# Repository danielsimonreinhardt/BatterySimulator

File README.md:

# BatterySimulator

Zellspannungs-Simulator für Tests von Batteriemanagement-Steuergeräten: 14 isolierte Zellkanäle (je 0–5 V, bis 0,5 A, zu einem
Stapel kaskadiert), ein Master mit S32K146, Bedienung über Drehgeber, Anzeige und Taster oder ferngesteuert per CAN (500 kbit/s).

| Ordner | Inhalt |
|---|---|
| [`Hardware/`](Hardware/) | Schaltpläne und Platinen (KiCad): Master, Zellkanal, Rückwand, Versorgung, dazu die Stückliste. |
| [`Firmware/`](Firmware/) | Firmware des Masters als neXtBSW-Kundenprojekt (`battsim_master`), mit Tests, Gerätetermin-Protokollen und Sicherheitshinweisen. |
| [`Doku/`](Doku/) | Analyse der alten Hard- und Firmware, Konzept, Reviews und Entscheidungen, CAN-Verhalten. Einstieg: [`Doku/README.md`](Doku/README.md). |

## Firmware klonen und bauen

neXtBSW liegt als Untermodul in `Firmware/nextbsw` (Repository `neXtBSW_development`, **privat**: ohne Zugriff schlägt das
Klonen des Untermoduls fehl). Auf Windows zählt die Pfadlänge (der längste Objektpfad des Baus misst gut 240 von 260 Zeichen),
deshalb dieses Repository möglichst weit oben im Dateisystem klonen, z. B. nach `C:\BatterySimulator`.

```sh
git clone --recurse-submodules https://github.com/danielsimonreinhardt/BatterySimulator.git C:/BatterySimulator
cd C:/BatterySimulator/Firmware
python nextbsw/tools/setup venv .
cmake --preset battsim-master
cmake --build --preset battsim-master
```

Weiter in [`Firmware/README.md`](Firmware/README.md).

## Lizenz

* **Firmware und Dokumentation** (`Firmware/`, `Doku/`): Apache License 2.0, siehe [`LICENSE`](LICENSE). Das Untermodul `Firmware/nextbsw` ist ein eigenes
  Repository und hat seine eigenen Bedingungen.
* **Hardware** (`Hardware/`): CERN Open Hardware Licence Version 2 – Permissive (CERN-OHL-P-2.0), siehe [`Hardware/LICENSE`](Hardware/LICENSE).

Schaltpläne und Platinen enthalten Symbole und Footprints aus den offiziellen KiCad-Bibliotheken (Lizenz: CC-BY-SA 4.0 mit der
KiCad-Ausnahme für Entwürfe, die diese Bibliotheken nur verwenden); sie bleiben dadurch unter deren Bedingungen, der Entwurf selbst unter CERN-OHL-P-2.0.

**Aufdruck auf den Platinen:** Auf den Platinen `BattSimMaster`, `BattSim_V1` und `BattSim_Supply` steht der Text „CREATED 11/2024 – ALL RIGHTS RESERVED“.
Er gilt nicht mehr: Für die Entwürfe in `Hardware/` gilt die CERN-OHL-P-2.0, auch wenn der Aufdruck auf bereits gefertigten Platinen etwas anderes sagt. Der Aufdruck wird mit der
nächsten Platinen-Revision angepasst; die KiCad-Quellen sind bis dahin unverändert.

## Stand

Firmware und Doku sind der Arbeitsstand der Entwicklung; ein Release gibt es nicht. Ein Gerät darf nur nach den
Sicherheitshinweisen in `Firmware/doc/` und `Doku/` angeschlossen und geflasht werden (kein Prüfling und keine Last an den
Zellklemmen beim Flashen).

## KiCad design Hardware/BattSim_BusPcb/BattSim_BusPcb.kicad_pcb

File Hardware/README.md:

# Hardware

KiCad-Quellen des Batterie-Simulators (je Ordner ein KiCad-Projekt) und die Stückliste. Lizenz: CERN-OHL-P-2.0, siehe [`LICENSE`](LICENSE).

| Ordner | Inhalt |
|---|---|
| `BattSimMaster/` | Master mit S32K146 (Blätter `BattSimMaster` und `MCU`) |
| `BattSim_V1/` | Zellkanal |
| `BattSim_BusPcb/` | Rückwand |
| `BattSim_Supply/` | Versorgung (230 V → 48 V → 5 V) |
| `BOM_gesamt.xlsx` | Stückliste aller Baugruppen |

Übernommen sind nur die Quellen (`.kicad_pro`, `.kicad_sch`, `.kicad_pcb`). Nicht dabei sind die 3D-Modelle (`.step`), die Fertigungsdaten (Gerber),
die KiCad-Sicherungen, die Simulationsdateien und Zwischenspeicher; die 3D-Modelle der Bauteile kommen aus den KiCad-Standardbibliotheken.
Die Quellen werden vom Nutzer außerhalb dieses Repositorys gepflegt und hier bei Bedarf nachgezogen.

Beschreibung der Hardware und Sicherheitsbefunde: [`../Doku/hardware-system.html`](../Doku/hardware-system.html) und
[`../Doku/hardware-zellkanal.html`](../Doku/hardware-zellkanal.html).

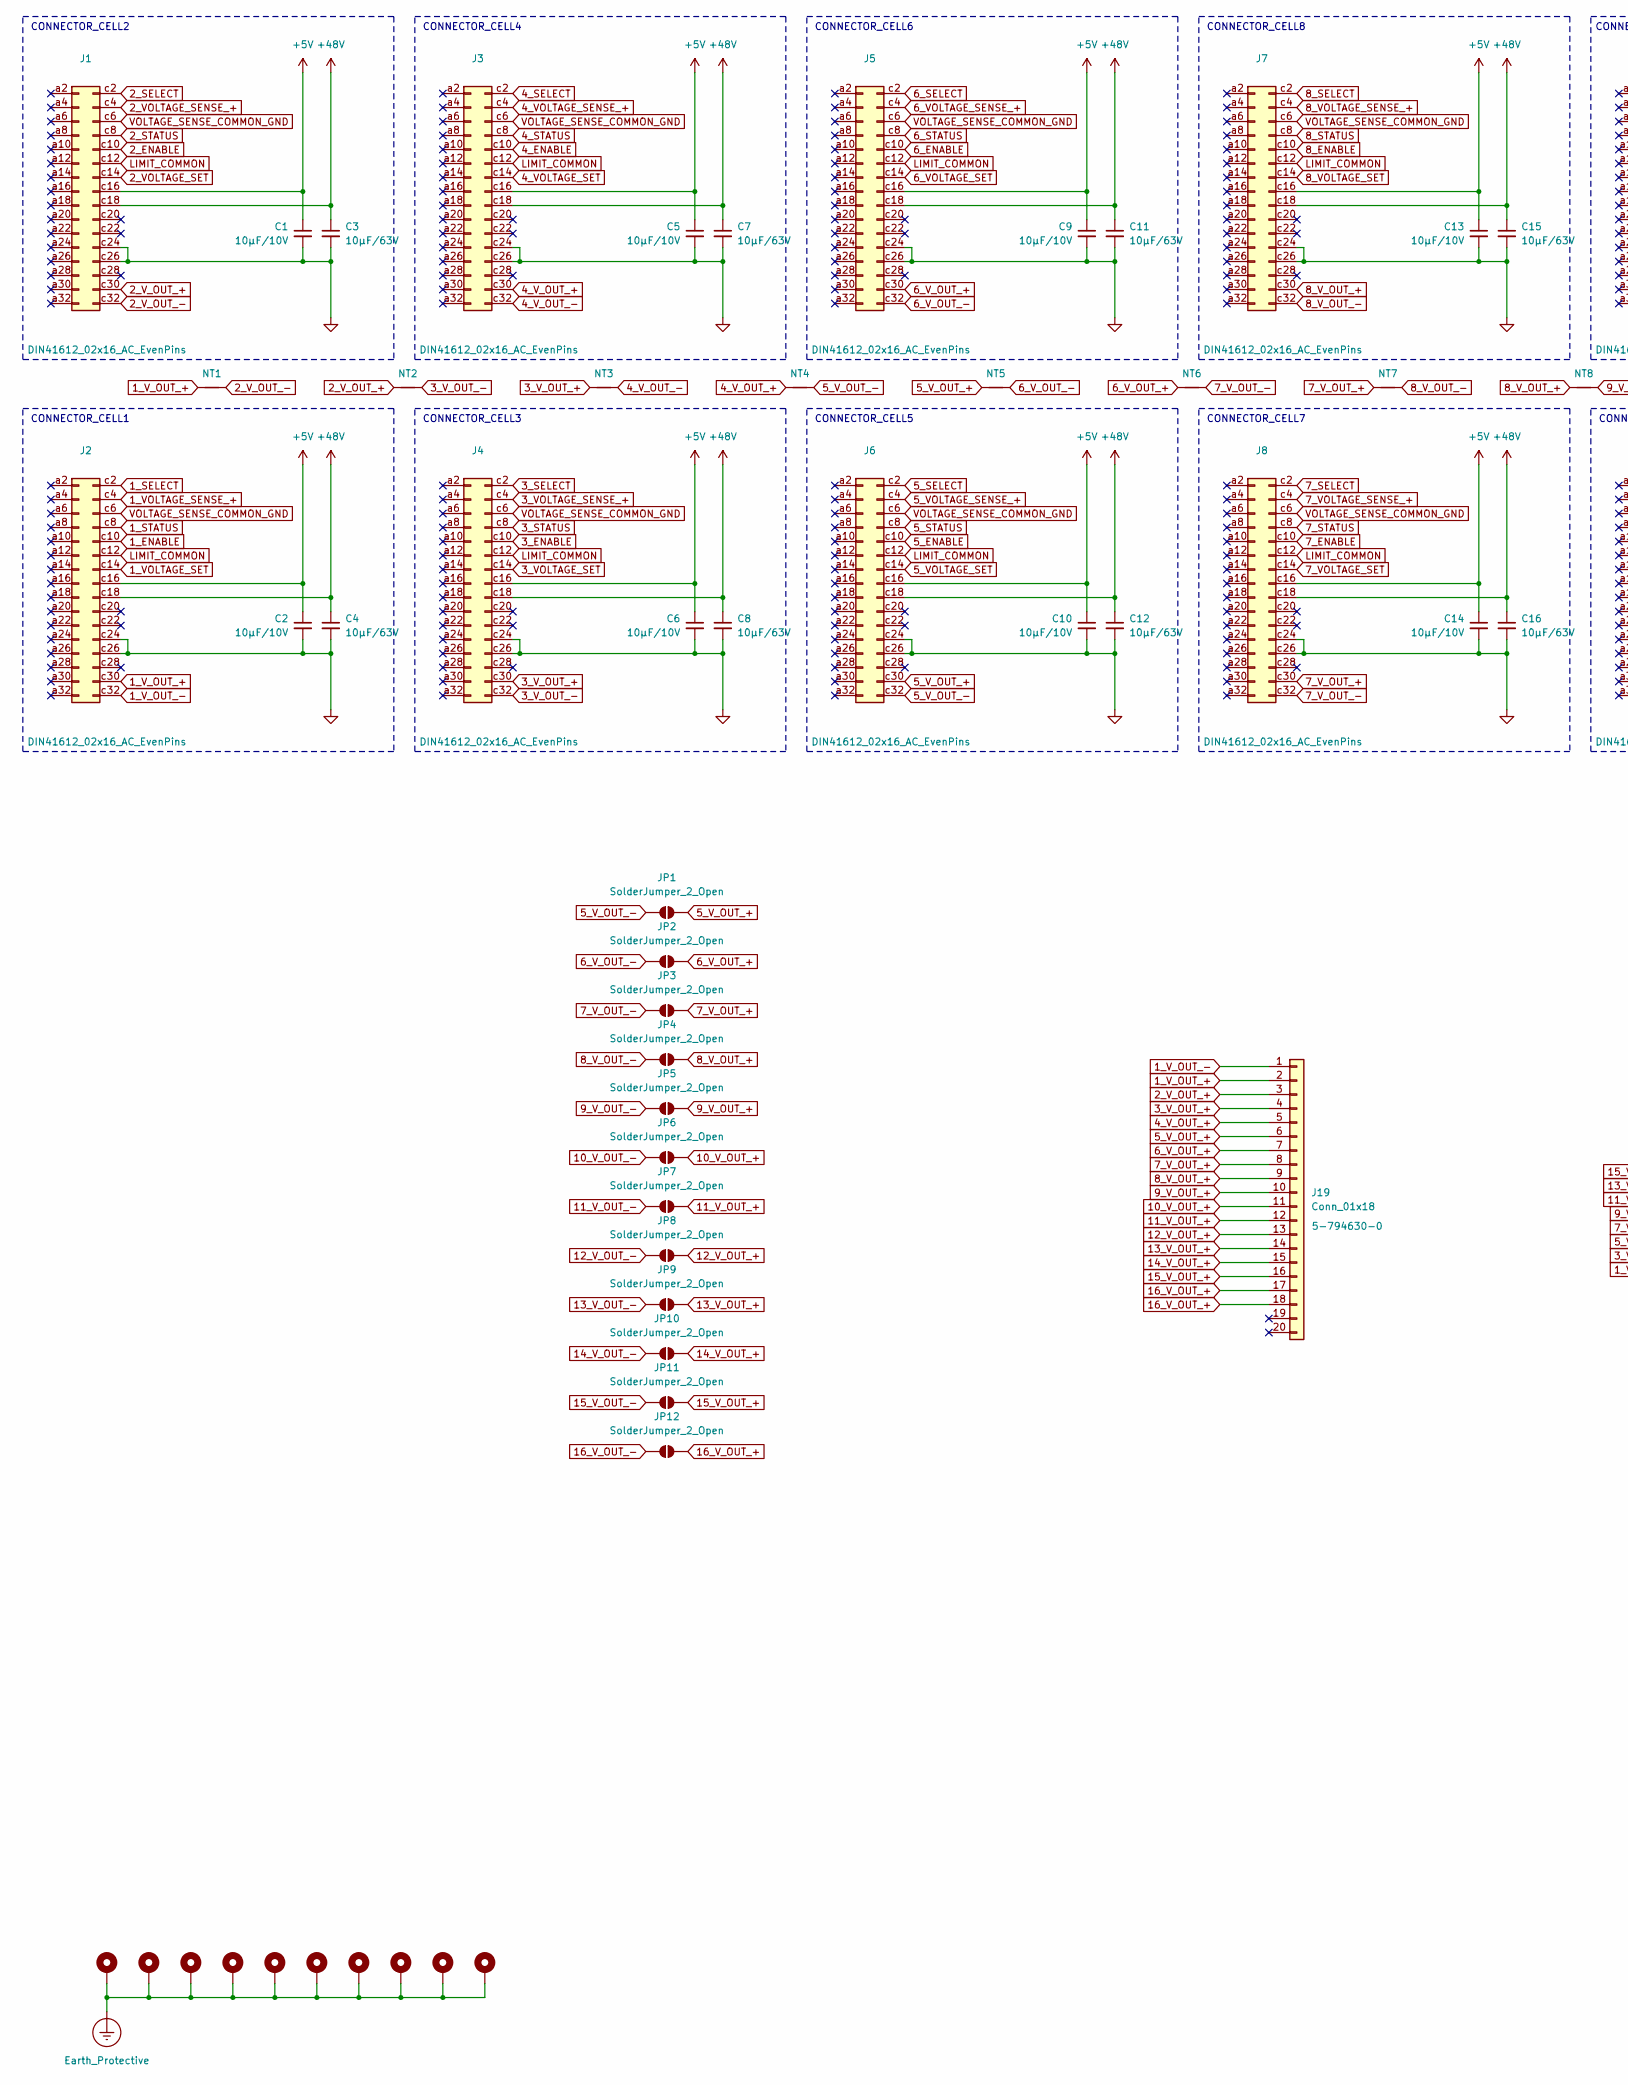
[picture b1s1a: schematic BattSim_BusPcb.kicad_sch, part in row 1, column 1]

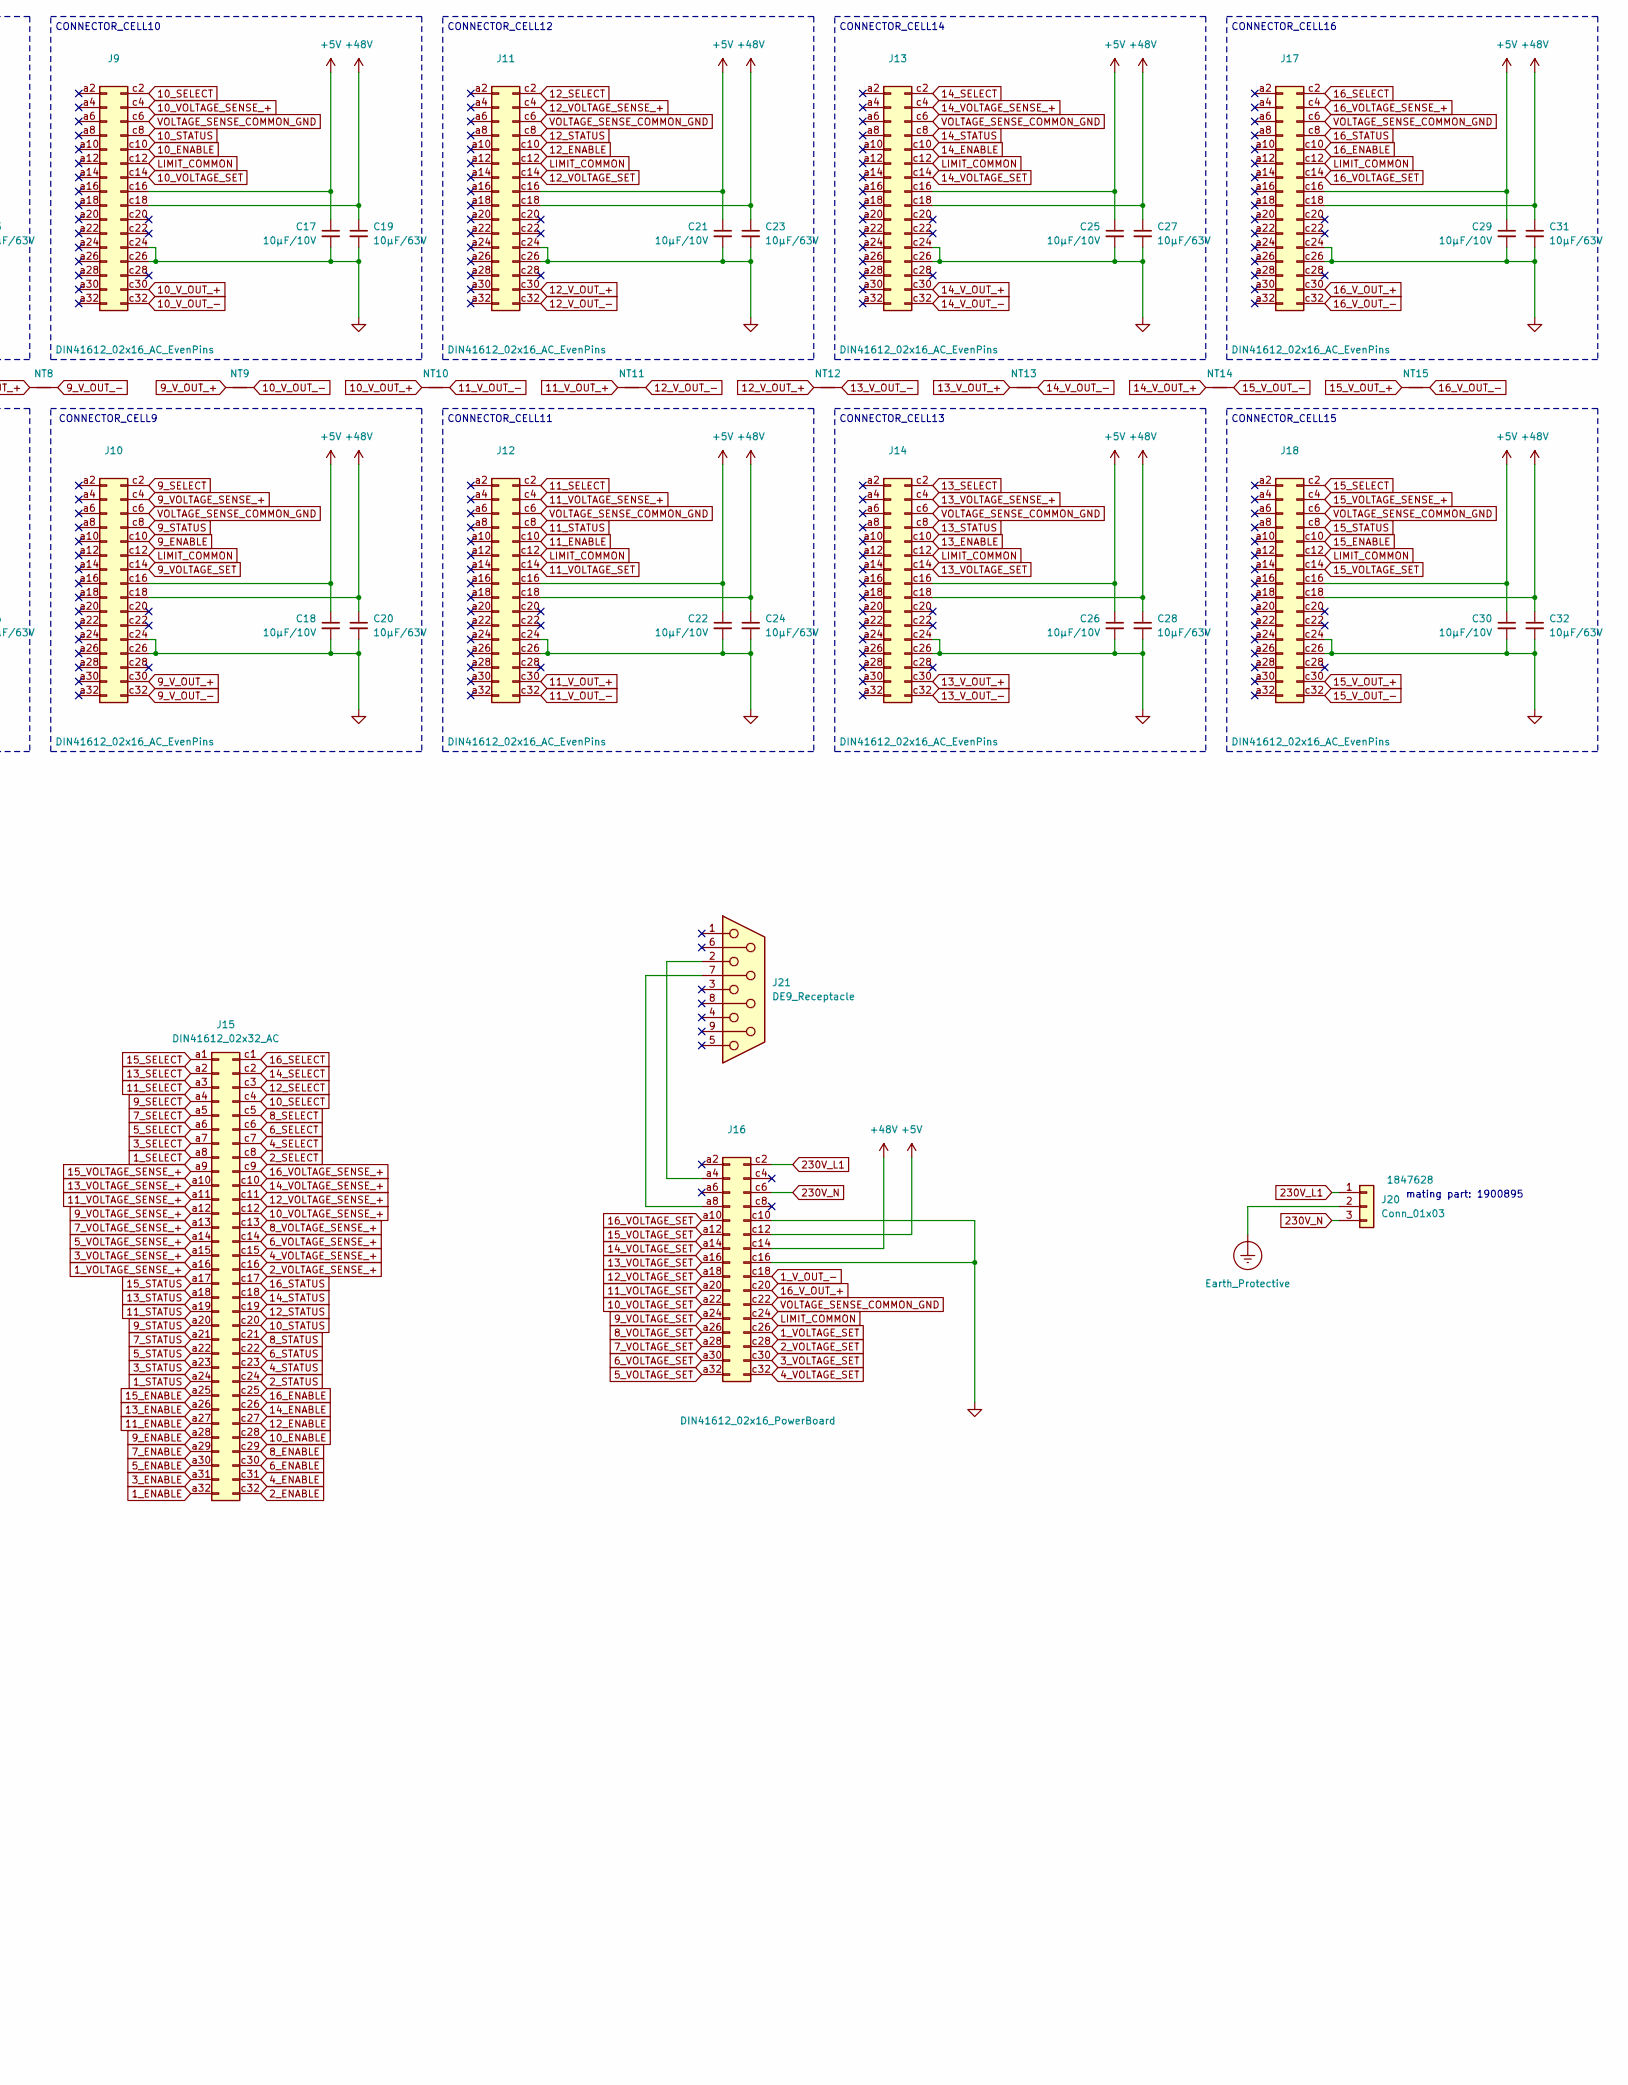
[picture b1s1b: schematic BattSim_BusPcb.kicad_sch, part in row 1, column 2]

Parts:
C1, C2, C5, C6, C9, C10, C13, C14, C17, C18, C21, C22, C25, C26, C29, C30: 10µF/10V; C_0805_2012Metric
C3, C4, C7, C8, C11, C12, C15, C16, C19, C20, C23, C24, C27, C28, C31, C32: 10µF/63V; C_1812_4532Metric
H1, H2, H3, H4, H5, H6, H7, H8, H9, H10: MountingHole_Pad; MountingHole_4.3x6.2mm_M4_Pad_Via
J1, J2, J3, J4, J5, J6, J7, J8, J9, J10, J11, J12, J13, J14, J17, J18: DIN41612_02x16_AC_EvenPins; DIN41612_C_2x16_Female_Vertical_THT
J15: DIN41612_02x32_AC; DIN41612_C_2x32_Female_Vertical_THT
J16: DIN41612_02x16_PowerBoard; DIN41612_C_2x16_Female_Vertical_THT
J19: Conn_01x18; 5-794630-0
J20: Conn_01x03; PhoenixContact_MCV_1,5_3-GF-5.08_1x03_P5.08mm_Vertical_Thre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
J21: DE9_Receptacle; DSUB-9_Female_Vertical_P2.77x2.84mm_MountingHoles
JP1, JP2, JP3, JP4, JP5, JP6, JP7, JP8, JP9, JP10, JP11, JP12: SolderJumper_2_Open; SolderJumper-2_P1.3mm_Open_RoundedPad1.0x1.5mm
NT1, NT2, NT3, NT4, NT5, NT6, NT7, NT8, NT9, NT10, NT11, NT12, NT13, NT14, NT15: NetTie_2; NetTie-2_THT_Pad1.0mm

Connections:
1_ENABLE: J2.c10, J15.a32
1_SELECT: J2.c2, J15.a8
1_STATUS: J2.c8, J15.a24
1_VOLTAGE_SENSE_+: J2.c4, J15.a16
1_VOLTAGE_SET: J2.c14, J16.c26
1_V_OUT_+: J2.c30, J19.2, NT1.1
1_V_OUT_-: J2.c32, J16.c18, J19.1
2_ENABLE: J1.c10, J15.c32
2_SELECT: J1.c2, J15.c8
2_STATUS: J1.c8, J15.c24
2_VOLTAGE_SENSE_+: J1.c4, J15.c16
2_VOLTAGE_SET: J1.c14, J16.c28
2_V_OUT_+: J1.c30, J19.3, NT2.1
2_V_OUT_-: J1.c32, NT1.2
3_ENABLE: J4.c10, J15.a31
3_SELECT: J4.c2, J15.a7
3_STATUS: J4.c8, J15.a23
3_VOLTAGE_SENSE_+: J4.c4, J15.a15
3_VOLTAGE_SET: J4.c14, J16.c30
3_V_OUT_+: J4.c30, J19.4, NT3.1
3_V_OUT_-: J4.c32, NT2.2
4_ENABLE: J3.c10, J15.c31
4_SELECT: J3.c2, J15.c7
4_STATUS: J3.c8, J15.c23
4_VOLTAGE_SENSE_+: J3.c4, J15.c15
4_VOLTAGE_SET: J3.c14, J16.c32
4_V_OUT_+: J3.c30, J19.5, NT4.1
4_V_OUT_-: J3.c32, NT3.2
5_ENABLE: J6.c10, J15.a30
5_SELECT: J6.c2, J15.a6
5_STATUS: J6.c8, J15.a22
5_VOLTAGE_SENSE_+: J6.c4, J15.a14
5_VOLTAGE_SET: J6.c14, J16.a32
5_V_OUT_+: J6.c30, J19.6, JP1.2 (B), NT5.1
5_V_OUT_-: J6.c32, JP1.1 (A), NT4.2
6_ENABLE: J5.c10, J15.c30
6_SELECT: J5.c2, J15.c6
6_STATUS: J5.c8, J15.c22
6_VOLTAGE_SENSE_+: J5.c4, J15.c14
6_VOLTAGE_SET: J5.c14, J16.a30
6_V_OUT_+: J5.c30, J19.7, JP2.2 (B), NT6.1
6_V_OUT_-: J5.c32, JP2.1 (A), NT5.2
7_ENABLE: J8.c10, J15.a29
7_SELECT: J8.c2, J15.a5
7_STATUS: J8.c8, J15.a21
7_VOLTAGE_SENSE_+: J8.c4, J15.a13
7_VOLTAGE_SET: J8.c14, J16.a28
7_V_OUT_+: J8.c30, J19.8, JP3.2 (B), NT7.1
7_V_OUT_-: J8.c32, JP3.1 (A), NT6.2
8_ENABLE: J7.c10, J15.c29
8_SELECT: J7.c2, J15.c5
8_STATUS: J7.c8, J15.c21
8_VOLTAGE_SENSE_+: J7.c4, J15.c13
8_VOLTAGE_SET: J7.c14, J16.a26
8_V_OUT_+: J7.c30, J19.9, JP4.2 (B), NT8.1
8_V_OUT_-: J7.c32, JP4.1 (A), NT7.2
9_ENABLE: J10.c10, J15.a28
9_SELECT: J10.c2, J15.a4
9_STATUS: J10.c8, J15.a20
9_VOLTAGE_SENSE_+: J10.c4, J15.a12
9_VOLTAGE_SET: J10.c14, J16.a24
9_V_OUT_+: J10.c30, J19.10, JP5.2 (B), NT9.1
9_V_OUT_-: J10.c32, JP5.1 (A), NT8.2
10_ENABLE: J9.c10, J15.c28
10_SELECT: J9.c2, J15.c4
10_STATUS: J9.c8, J15.c20
10_VOLTAGE_SENSE_+: J9.c4, J15.c12
10_VOLTAGE_SET: J9.c14, J16.a22
10_V_OUT_+: J9.c30, J19.11, JP6.2 (B), NT10.1
10_V_OUT_-: J9.c32, JP6.1 (A), NT9.2
11_ENABLE: J12.c10, J15.a27
11_SELECT: J12.c2, J15.a3
11_STATUS: J12.c8, J15.a19
11_VOLTAGE_SENSE_+: J12.c4, J15.a11
11_VOLTAGE_SET: J12.c14, J16.a20
11_V_OUT_+: J12.c30, J19.12, JP7.2 (B), NT11.1
11_V_OUT_-: J12.c32, JP7.1 (A), NT10.2
12_ENABLE: J11.c10, J15.c27
12_SELECT: J11.c2, J15.c3
12_STATUS: J11.c8, J15.c19
12_VOLTAGE_SENSE_+: J11.c4, J15.c11
12_VOLTAGE_SET: J11.c14, J16.a18
12_V_OUT_+: J11.c30, J19.13, JP8.2 (B), NT12.1
12_V_OUT_-: J11.c32, JP8.1 (A), NT11.2
13_ENABLE: J14.c10, J15.a26
13_SELECT: J14.c2, J15.a2
13_STATUS: J14.c8, J15.a18
13_VOLTAGE_SENSE_+: J14.c4, J15.a10
13_VOLTAGE_SET: J14.c14, J16.a16
13_V_OUT_+: J14.c30, J19.14, JP9.2 (B), NT13.1
13_V_OUT_-: J14.c32, JP9.1 (A), NT12.2
14_ENABLE: J13.c10, J15.c26
14_SELECT: J13.c2, J15.c2
14_STATUS: J13.c8, J15.c18
14_VOLTAGE_SENSE_+: J13.c4, J15.c10
14_VOLTAGE_SET: J13.c14, J16.a14
14_V_OUT_+: J13.c30, J19.15, JP10.2 (B), NT14.1
14_V_OUT_-: J13.c32, JP10.1 (A), NT13.2
15_ENABLE: J15.a25, J18.c10
15_SELECT: J15.a1, J18.c2
15_STATUS: J15.a17, J18.c8
15_VOLTAGE_SENSE_+: J15.a9, J18.c4
15_VOLTAGE_SET: J16.a12, J18.c14
15_V_OUT_+: J18.c30, J19.16, JP11.2 (B), NT15.1
15_V_OUT_-: J18.c32, JP11.1 (A), NT14.2
16_ENABLE: J15.c25, J17.c10
16_SELECT: J15.c1, J17.c2
16_STATUS: J15.c17, J17.c8
16_VOLTAGE_SENSE_+: J15.c9, J17.c4
16_VOLTAGE_SET: J16.a10, J17.c14
16_V_OUT_+: J16.c20, J17.c30, J19.17, J19.18, JP12.2 (B)
16_V_OUT_-: J17.c32, JP12.1 (A), NT15.2
230V_L1: J16.c2, J20.1
230V_N: J16.c6, J20.3
+5V: C1.1, C2.1, C5.1, C6.1, C9.1, C10.1, C13.1, C14.1, C17.1, C18.1, C21.1, C22.1, C25.1, C26.1, C29.1, C30.1, J1.c16, J2.c16, J3.c16, J4.c16, J5.c16, J6.c16, J7.c16, J8.c16, J9.c16, J10.c16, J11.c16, J12.c16, J13.c16, J14.c16, J16.c12, J17.c16, J18.c16
+48V: C3.1, C4.1, C7.1, C8.1, C11.1, C12.1, C15.1, C16.1, C19.1, C20.1, C23.1, C24.1, C27.1, C28.1, C31.1, C32.1, J1.c18, J2.c18, J3.c18, J4.c18, J5.c18, J6.c18, J7.c18, J8.c18, J9.c18, J10.c18, J11.c18, J12.c18, J13.c18, J14.c18, J16.c14, J17.c18, J18.c18
Earth_Protective: H1.1, H2.1, H3.1, H4.1, H5.1, H6.1, H7.1, H8.1, H9.1, H10.1, J20.2
GND: C1.2, C2.2, C3.2, C4.2, C5.2, C6.2, C7.2, C8.2, C9.2, C10.2, C11.2, C12.2, C13.2, C14.2, C15.2, C16.2, C17.2, C18.2, C19.2, C20.2, C21.2, C22.2, C23.2, C24.2, C25.2, C26.2, C27.2, C28.2, C29.2, C30.2, C31.2, C32.2, J1.c24, J1.c26, J2.c24, J2.c26, J3.c24, J3.c26, J4.c24, J4.c26, J5.c24, J5.c26, J6.c24, J6.c26, J7.c24, J7.c26, J8.c24, J8.c26, J9.c24, J9.c26, J10.c24, J10.c26, J11.c24, J11.c26, J12.c24, J12.c26, J13.c24, J13.c26, J14.c24, J14.c26, J16.c10, J16.c16, J17.c24, J17.c26, J18.c24, J18.c26
LIMIT_COMMON: J1.c12, J2.c12, J3.c12, J4.c12, J5.c12, J6.c12, J7.c12, J8.c12, J9.c12, J10.c12, J11.c12, J12.c12, J13.c12, J14.c12, J16.c24, J17.c12, J18.c12
unnamed: J16.a4, J21.2
unnamed: J16.a8, J21.7
VOLTAGE_SENSE_COMMON_GND: J1.c6, J2.c6, J3.c6, J4.c6, J5.c6, J6.c6, J7.c6, J8.c6, J9.c6, J10.c6, J11.c6, J12.c6, J13.c6, J14.c6, J16.c22, J17.c6, J18.c6

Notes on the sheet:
CONNECTOR_CELL12
CONNECTOR_CELL15
CONNECTOR_CELL2
CONNECTOR_CELL10
mating part: 1900895
CONNECTOR_CELL7
CONNECTOR_CELL8
CONNECTOR_CELL3
CONNECTOR_CELL4
CONNECTOR_CELL1
CONNECTOR_CELL6
CONNECTOR_CELL11
CONNECTOR_CELL9
CONNECTOR_CELL14
CONNECTOR_CELL16
CONNECTOR_CELL5
CONNECTOR_CELL13

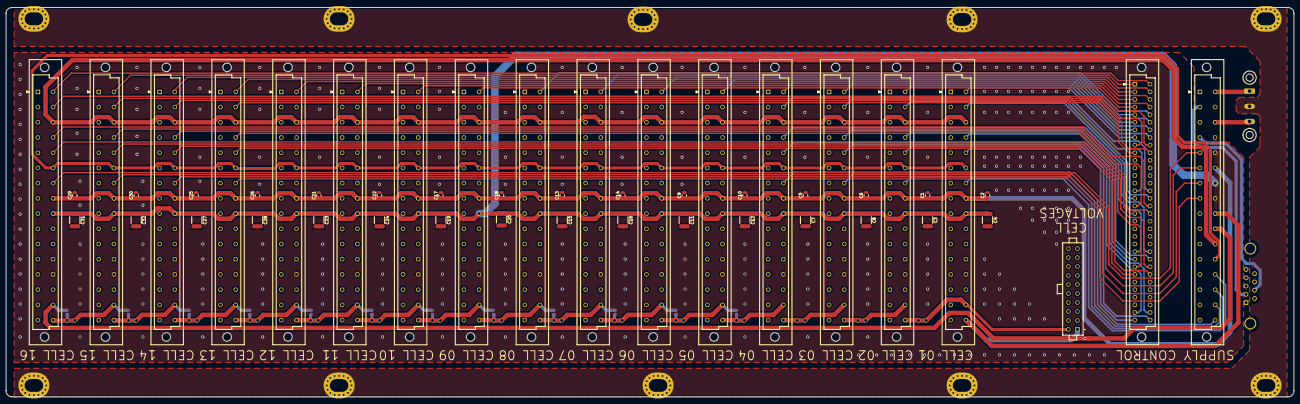
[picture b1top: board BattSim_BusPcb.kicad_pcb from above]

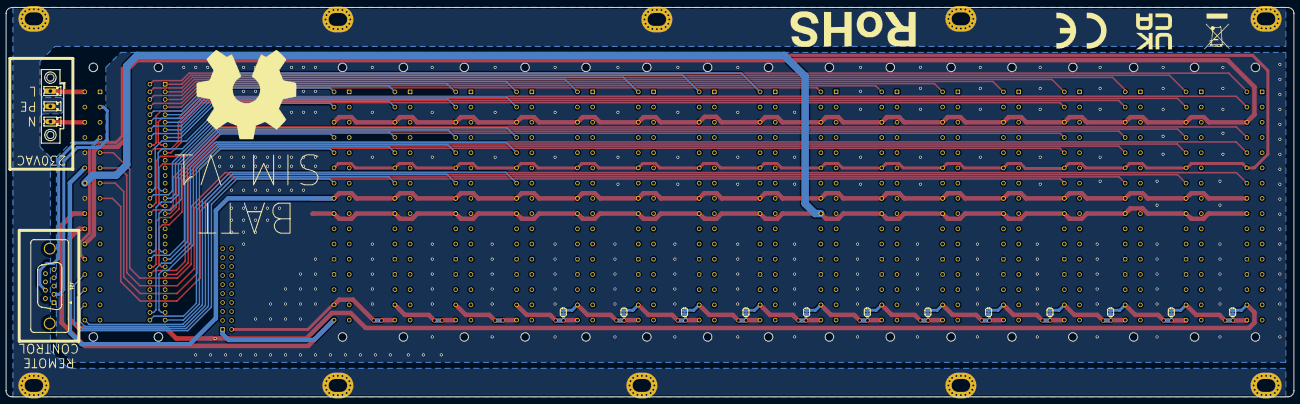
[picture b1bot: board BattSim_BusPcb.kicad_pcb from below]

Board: 4 copper layers, 430.0 x 130.0 mm, 90 parts (14 on the bottom side), 122 nets.

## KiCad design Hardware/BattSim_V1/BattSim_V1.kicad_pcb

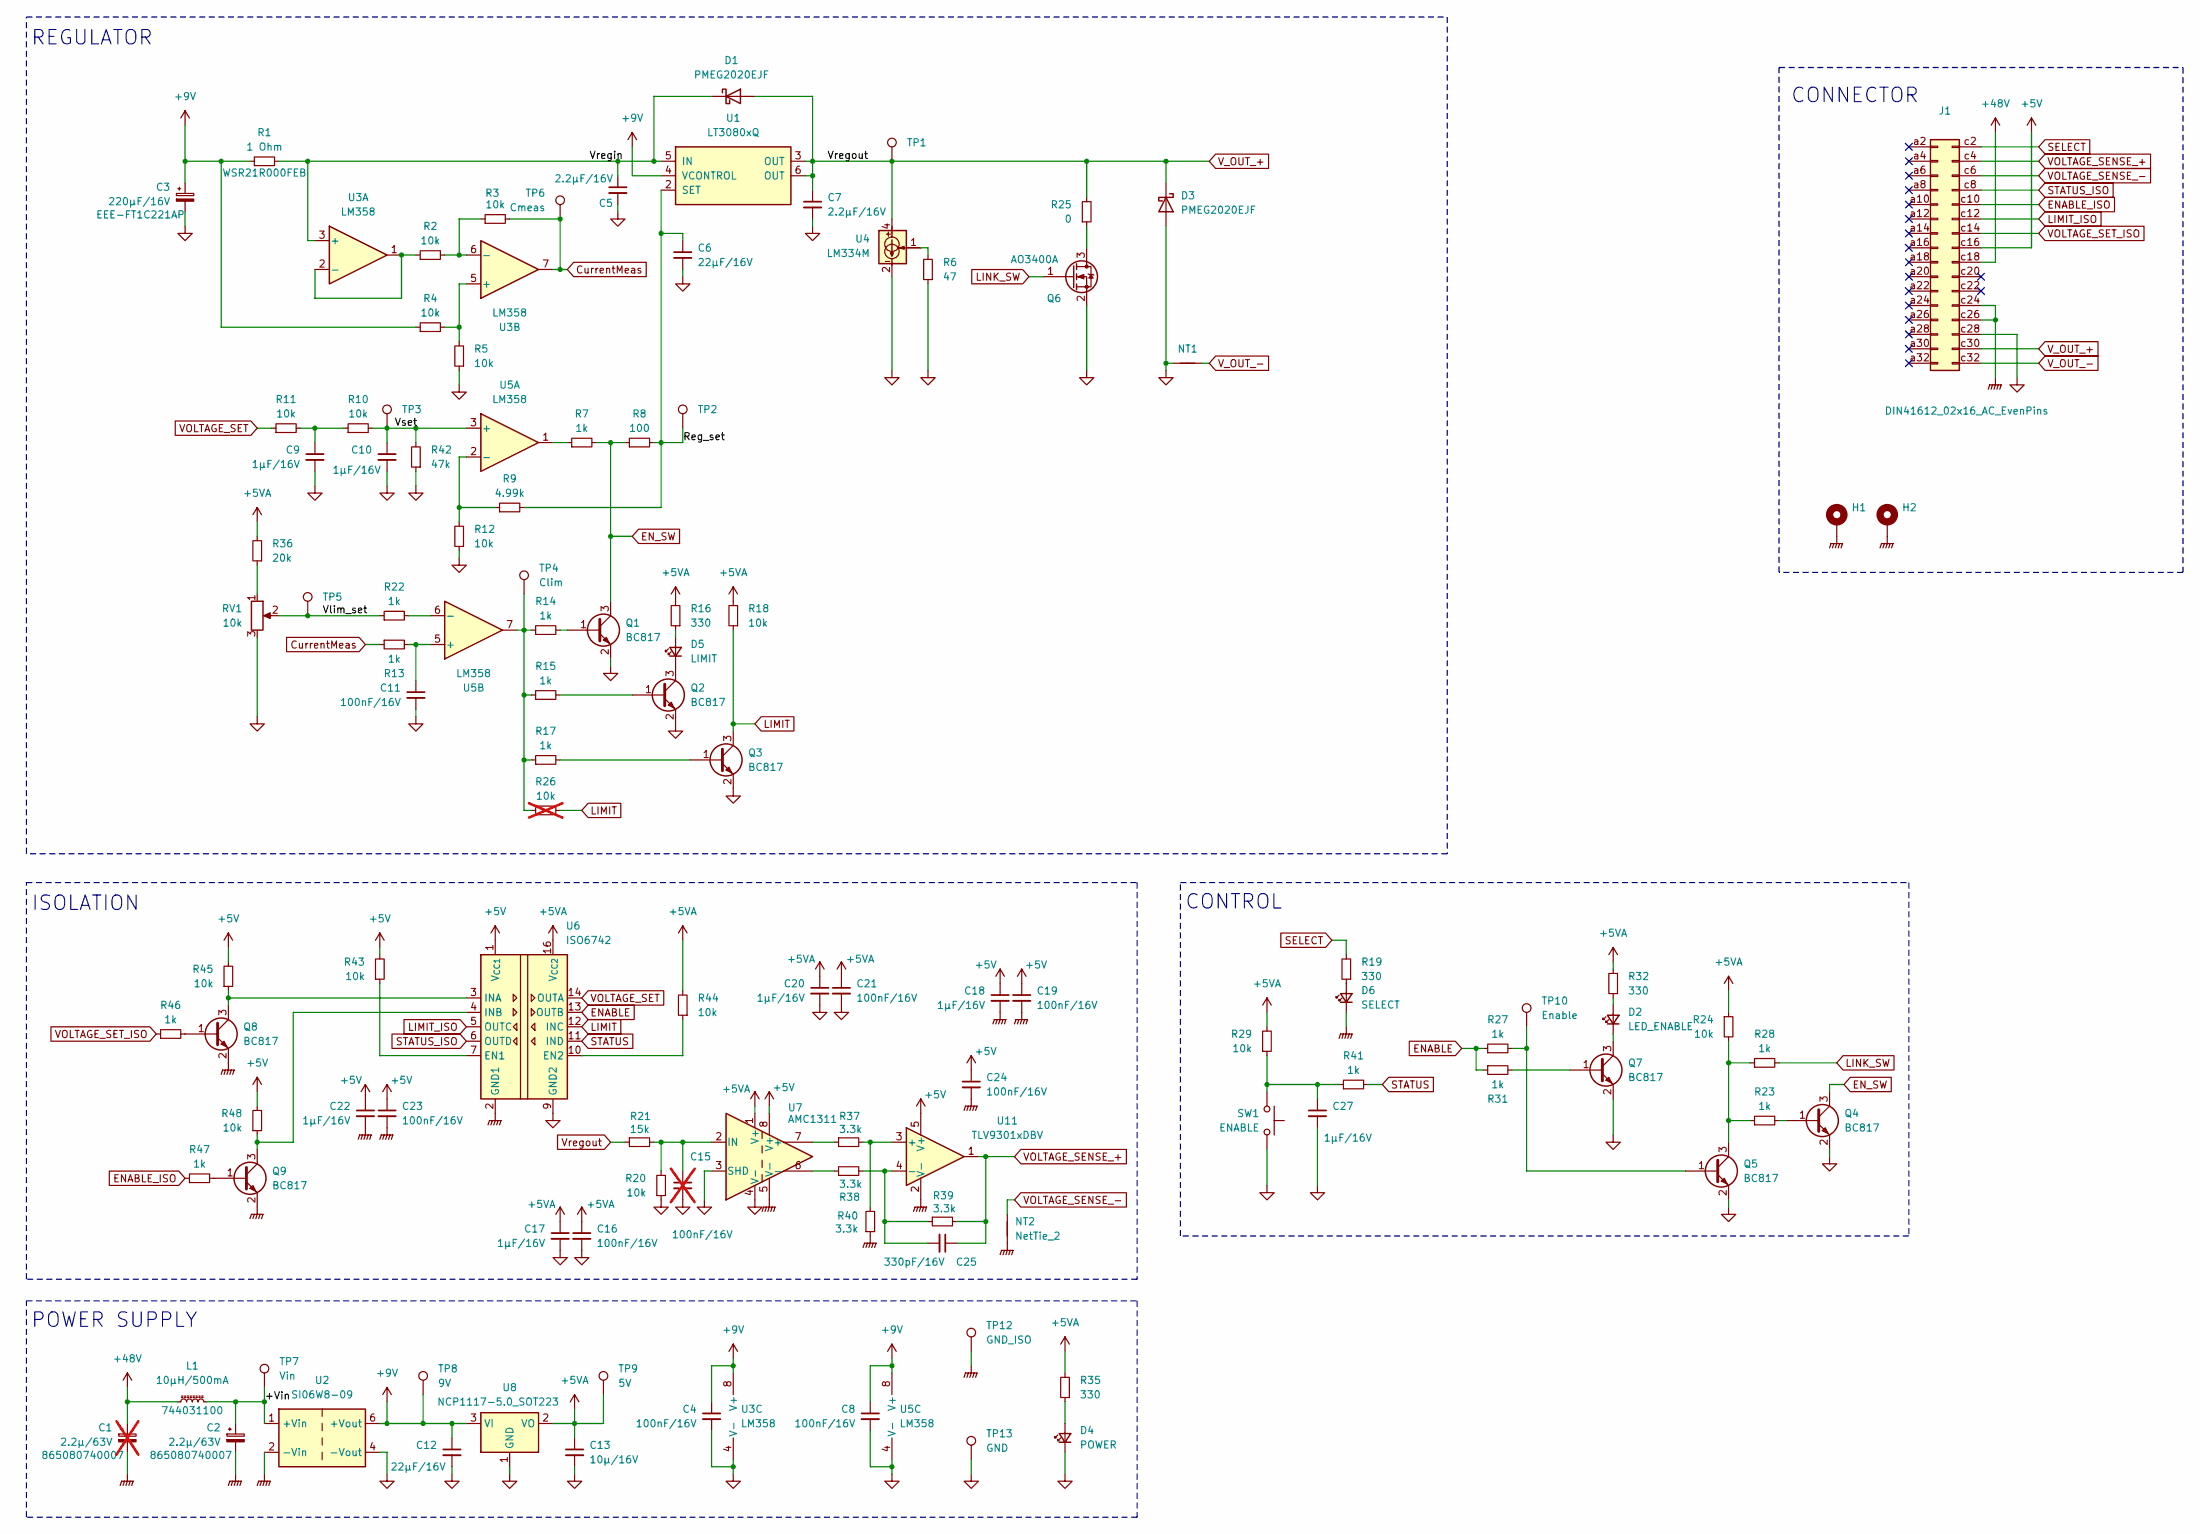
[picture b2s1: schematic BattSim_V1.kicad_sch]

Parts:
C1: 2.2µ/63V; CP_Elec_4x5.4; LCSC Part # C249627; not fitted
C2: 2.2µ/63V; CP_Elec_4x5.4; LCSC Part # C249627
C3: 220µF/16V; CP_Elec_6.3x5.8; LCSC Part # C2977551
C4, C8, C11, C16, C19, C21, C23, C24: 100nF/16V; C_0603_1608Metric; LCSC Part # C14663
C5, C7: 2.2µF/16V; C_0805_2012Metric; LCSC Part # C28234
C6, C12: 22µF/16V; C_1206_3216Metric; LCSC Part # C77088
C9, C10, C17, C18, C20, C22, C27: 1µF/16V; C_0603_1608Metric; LCSC Part # C15849
C13: 10µ/16V; C_0805_2012Metric; LCSC Part # C15850
C15: 100nF/16V; C_0603_1608Metric; not fitted
C25: 330pF/16V; C_0603_1608Metric
D1, D3: PMEG2020EJF; D_SOD-323F; LCSC Part # C50704
D2: LED_ENABLE; LED_D3.0mm_Horizontal_O1.27mm_Z6.0mm
D4: POWER; LED_D3.0mm_Horizontal_O1.27mm_Z6.0mm
D5: LIMIT; LED_D3.0mm_Horizontal_O1.27mm_Z6.0mm
D6: SELECT; LED_D3.0mm_Horizontal_O1.27mm_Z6.0mm
H1, H2: MountingHole_Pad; MountingHole_2.7mm_M2.5_ISO14580_Pad_TopBottom
J1: DIN41612_02x16_AC_EvenPins; DIN41612_C_2x16_Male_Horizontal_THT
L1: 10µH/500mA; L_Wuerth_WE-TPC-3816; LCSC Part # C2045791
NT1, NT2: NetTie_2; NetTie-2_SMD_Pad0.5mm
Q1, Q2, Q3, Q4, Q5, Q7, Q8, Q9: BC817; SOT-23; LCSC Part # C52801
Q6: AO3400A; SOT-23; LCSC Part # C20917
R1: 1 Ohm; R_Shunt_Vishay_WSR2_WSR3_KelvinConnection
R2, R3, R4, R5, R10, R11, R12, R18, R20, R24, R29, R43, R44, R45, R48: 10k; R_0603_1608Metric; LCSC Part # C25804
R6: 47; R_0603_1608Metric; LCSC Part # C1211
R7, R13, R14, R15, R17, R22, R23, R27, R28, R31, R41, R46, R47: 1k; R_0603_1608Metric; LCSC Part # C21190
R8: 100; R_0603_1608Metric; LCSC Part # C22775
R9: 4.99k; R_0603_1608Metric; LCSC Part # C23046
R16, R19, R32, R35: 330; R_0603_1608Metric; LCSC Part # C23138
R21: 15k; R_0603_1608Metric
R25: 0; R_0805_2012Metric; LCSC Part # C17477
R26: 10k; R_0603_1608Metric; LCSC Part # C25804; not fitted
R36: 20k; R_0603_1608Metric; LCSC Part # C4184
R37, R38, R39, R40: 3.3k; R_0603_1608Metric; LCSC Part # C22978
R42: 47k; R_0603_1608Metric
RV1: 10k; Potentiometer_Piher_PT-10-V10_Vertical_Hole
SW1: ENABLE; SW_Tactile_SPST_Angled_PTS645Vx83-2LFS
TP1: Vregout; TestPoint_Pad_D1.0mm
TP2: Reg_set; TestPoint_Pad_D1.0mm
TP3: Vset; TestPoint_Pad_D1.0mm
TP4: Clim; TestPoint_Pad_D1.0mm
TP5: Vlim_set; TestPoint_Pad_D1.0mm
TP6: Cmeas; TestPoint_Pad_D1.0mm
TP7: Vin; TestPoint_Pad_D1.0mm
TP8: 9V; TestPoint_Pad_D1.0mm
TP9: 5V; TestPoint_Pad_D1.0mm
TP10: Enable; TestPoint_Pad_D1.0mm
TP12: GND_ISO; TestPoint_Loop_D1.80mm_Drill1.0mm_Beaded
TP13: GND; TestPoint_Loop_D1.80mm_Drill1.0mm_Beaded
U1: LT3080xQ; TO-263-5_TabPin3; LCSC Part # C670298
U2: SI06W8-09; Converter_DCDC_MeanWell_xI06W8
U3, U5: LM358; SOIC-8_3.9x4.9mm_P1.27mm; LCSC Part # C398914
U4: LM334M; SOIC-8_3.9x4.9mm_P1.27mm; LCSC Part # C7945
U6: ISO6742; SOIC-16W_7.5x10.3mm_P1.27mm; LCSC Part # C5216407
U7: AMC1311; SOIC-8_7.5x5.85mm_P1.27mm; LCSC Part # C783598
U8: NCP1117-5.0_SOT223; SOT-223-3_TabPin2; LCSC Part # C6187
U11: TLV9301xDBV; SOT-23-5; LCSC Part # C2867945

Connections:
+5V: C18.1, C19.1, C22.1, C23.1, C24.1, J1.c16, R43.2, R45.2, R48.2, U6.1 (V_{CC1}), U7.8 (V+), U11.5 (V+)
+5VA: C13.1, C16.1, C17.1, C20.1, C21.1, R16.2, R18.2, R24.1, R29.2, R32.2, R35.2, R36.2, R44.2, TP9.1, U6.16 (V_{CC2}), U7.1 (V+), U8.2 (VO)
+9V: C3.1, C4.1, C8.1, C12.1, R1.1, R4.1, TP8.1, U1.4 (VCONTROL), U2.6 (+Vout), U3.8 (V+), U5.8 (V+), U8.3 (VI)
+48V: C1.1, J1.c18, L1.1
/+Vin: C2.1, L1.2, TP7.1, U2.1 (+Vin)
/Reg_set: C6.1, R8.2, R9.2, TP2.1, U1.2 (SET)
/Vlim_set: R22.1, RV1.2, TP5.1
/Vregin: C5.1, D1.1 (K), R1.2, U1.5 (IN), U3.3 (+)
/Vset: C10.1, R10.2, R42.2, TP3.1, U5.3 (+)
CurrentMeas: R3.2, R13.1, TP6.1, U3.7
ENABLE: R27.1, R31.1, U6.13 (OUTB)
ENABLE_ISO: J1.c10, R47.1
EN_SW: Q1.3 (C), Q4.3 (C), R7.2, R8.1
GND: C3.2, C4.2, C5.2, C6.2, C7.2, C8.2, C9.2, C10.2, C11.2, C12.2, C13.2, C15.2, C16.2, C17.2, C20.2, C21.2, C27.2, D3.2 (A), D4.1 (K), J1.c28, NT1.1, Q1.2 (E), Q2.2 (E), Q3.2 (E), Q4.2 (E), Q5.2 (E), Q6.2 (S), Q7.2 (E), R5.1, R6.1, R12.1, R20.1, R42.1, RV1.3, SW1.1, TP13.1, U2.4 (-Vout), U3.4 (V-), U4.2, U4.3, U4.6, U4.7, U5.4 (V-), U6.9 (GND2), U6.15 (GND2), U7.3 (SHD), U7.4 (V-), U8.1 (GND)
GNDPWR: C1.2, C2.2, C18.2, C19.2, C22.2, C23.2, C24.2, D6.1 (K), H1.1, H2.1, J1.c24, J1.c26, NT2.1, Q8.2 (E), Q9.2 (E), R40.1, TP12.1, U2.2 (-Vin), U6.2 (GND1), U6.8 (GND1), U7.5 (V-), U11.2 (V-)
LIMIT: Q3.3 (C), R18.1, R26.2, U6.12 (INC)
LIMIT_ISO: J1.c12, U6.5 (OUTC)
LINK_SW: Q6.1 (G), R28.2
unnamed: C9.1, R10.1, R11.2
unnamed: C27.1, R29.1, R41.1, SW1.2
unnamed: D2.2 (A), R32.1
unnamed: D2.1 (K), Q7.3 (C)
unnamed: D4.2 (A), R35.1
unnamed: D5.2 (A), R16.1
unnamed: D5.1 (K), Q2.3 (C)
unnamed: D6.2 (A), R19.1
unnamed: Q1.1 (B), R14.2
unnamed: Q2.1 (B), R15.2
unnamed: Q3.1 (B), R17.2
unnamed: Q4.1 (B), R23.2
unnamed: Q5.1 (B), R27.2, TP10.1
unnamed: Q5.3 (C), R23.1, R24.2, R28.1
unnamed: Q6.3 (D), R25.1
unnamed: Q7.1 (B), R31.2
unnamed: Q8.1 (B), R46.2
unnamed: Q8.3 (C), R45.1, U6.3 (INA)
unnamed: Q9.1 (B), R47.2
unnamed: Q9.3 (C), R48.1, U6.4 (INB)
unnamed: R6.2, U4.1
unnamed: R7.1, U5.1
unnamed: R14.1, R15.1, R17.1, R26.1, TP4.1, U5.7
unnamed: R36.1, RV1.1
unnamed: R2.1, U3.1, U3.2 (-)
unnamed: R4.2, R5.2, U3.5 (+)
unnamed: R2.2, R3.1, U3.6 (-)
unnamed: R9.1, R12.2, U5.2 (-)
unnamed: C11.1, R13.2, U5.5 (+)
unnamed: R22.2, U5.6 (-)
unnamed: R43.1, U6.7 (EN1)
unnamed: R44.1, U6.10 (EN2)
unnamed: R37.1, U7.7 (+)
unnamed: R38.1, U7.6 (-)
unnamed: C15.1, R20.2, R21.2, U7.2 (IN)
unnamed: R37.2, R40.2, U11.3 (+)
unnamed: C25.2, R38.2, R39.1, U11.4 (-)
SELECT: J1.c2, R19.2
STATUS: R41.2, U6.11 (IND)
STATUS_ISO: J1.c8, U6.6 (OUTD)
VOLTAGE_SENSE_+: C25.1, J1.c4, R39.2, U11.1
VOLTAGE_SENSE_-: J1.c6, NT2.2
VOLTAGE_SET: R11.1, U6.14 (OUTA)
VOLTAGE_SET_ISO: J1.c14, R46.1
V_OUT_+: C7.1, D1.2 (A), D3.1 (K), J1.c30, R21.1, R25.2, TP1.1, U1.3 (OUT), U1.6 (OUT), U4.4
V_OUT_-: J1.c32, NT1.2

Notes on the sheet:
CONNECTOR
CONTROL
POWER SUPPLY
ISOLATION
REGULATOR

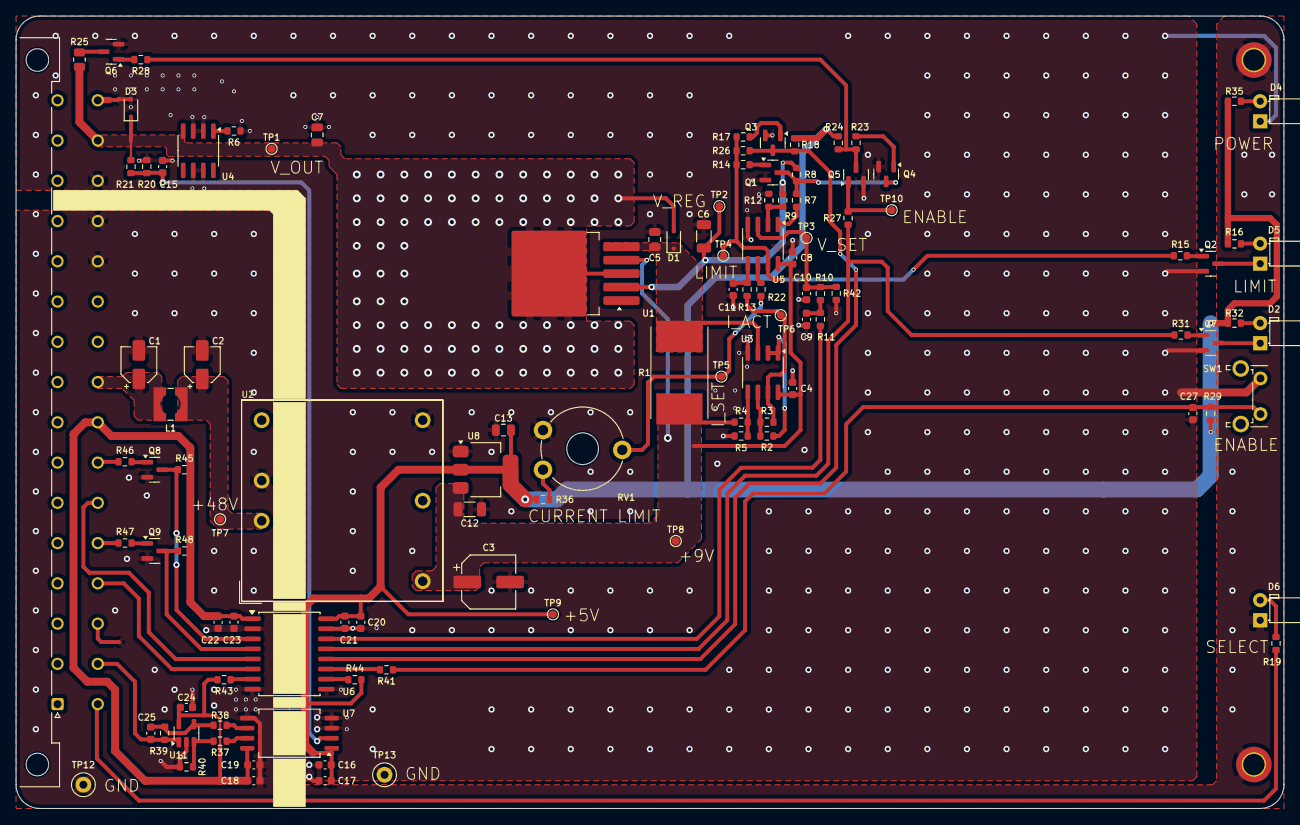
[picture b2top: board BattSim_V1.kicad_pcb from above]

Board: 2 copper layers, 160.0 x 100.0 mm, 114 parts (0 on the bottom side), 64 nets.

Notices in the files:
boards/battsim_master_v1/board.yaml:
SPDX-License-Identifier: Apache-2.0 WITH AdditionRef-neXtBSW-Generator-Output-Exception
